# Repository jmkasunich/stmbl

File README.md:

Build Log: https://travis-ci.org/rene-dev/stmbl

DISCLAIMER
===

THE AUTHORS OF THIS SOFTWARE ACCEPT ABSOLUTELY NO LIABILITY FOR
ANY HARM OR LOSS RESULTING FROM ITS USE.  IT IS _EXTREMELY_ UNWISE
TO RELY ON SOFTWARE ALONE FOR SAFETY.  Any machinery capable of
harming persons must have provisions for completely removing power
from all motors, etc, before persons enter any danger area.  All
machinery must be designed to comply with local and national safety
codes, and the authors of this software can not, and do not, take
any responsibility for such compliance.

This software is released under the GPLv3.

stmbl
=====

IMPORTANT:  This fork should **NOT** be used to make PC boards.
The board layout files have been reverted to work with the stable version of Kicad, which affects the copper.  At some point I will probably clean up the resulting issues, but that is not a priority.  I simply want to be able to view the layout using the stable version.

There is a wiki. https://github.com/rene-dev/stmbl/wiki
There will be documentation.

**IRC: #stmbl on irc.hackint.eu**
https://webirc.hackint.org/#stmbl

stmbl is an open source servo drive designed for Retrofitting CNC machines and Robots. It supports Industrial AC and DC servos with up to 320V and 2kW (see [specs](https://github.com/rene-dev/stmbl/wiki/specs) for details).

Documentation about the PCB and pinout of the feedback connector:

https://github.com/rene-dev/stmbl/wiki/Pinouts

https://github.com/rene-dev/stmbl/wiki/PCB

##### Hardware version 4.0

##### Driving a Bosch Turboscara
https://www.youtube.com/watch?v=d6NH1W7DUnQ

##### Driving a Manutec Robot
https://www.youtube.com/watch?v=gwgnAeGjZrA  
https://www.youtube.com/watch?v=wXLcAZwjlzE

##### Drivetest
https://www.youtube.com/watch?v=-E1o_5cFyto

#### Supported Motors
* Synchronous AC Servos
* DC Servos
* 2 Phase HF spindle motors
* IRAMX Hardware testet up to 320V

#### Supported Feedback systems
* Resolvers
* Incremental encoders
* sin/cos encoder interpolation
* Mitsubishi absolute encoders
* Sanyo Denki absolute encoders
* Yaskawa absolute encoders
* Sick HIPERFACE®

##### Planned:
* EnDat
* BiSS
* SSI
* Sanyo Denki wire-saving incremental encoder

#### Supported Position/Velocity Commands Inputs:
* Smartserial
* Quadrature
* Step/direction
* RS485

#### TODO
* AC Async

#### Directories
* hw/eagle/ Eagle board files and schematics
* hw/spice/ Spice simulation for resolver interface
* src/ STM32F4 code, command, feedback and control loop
* stm32f103/ STM32F1 code, running on the HV side, generating PWM
* bootloader/ bootloader for the f4

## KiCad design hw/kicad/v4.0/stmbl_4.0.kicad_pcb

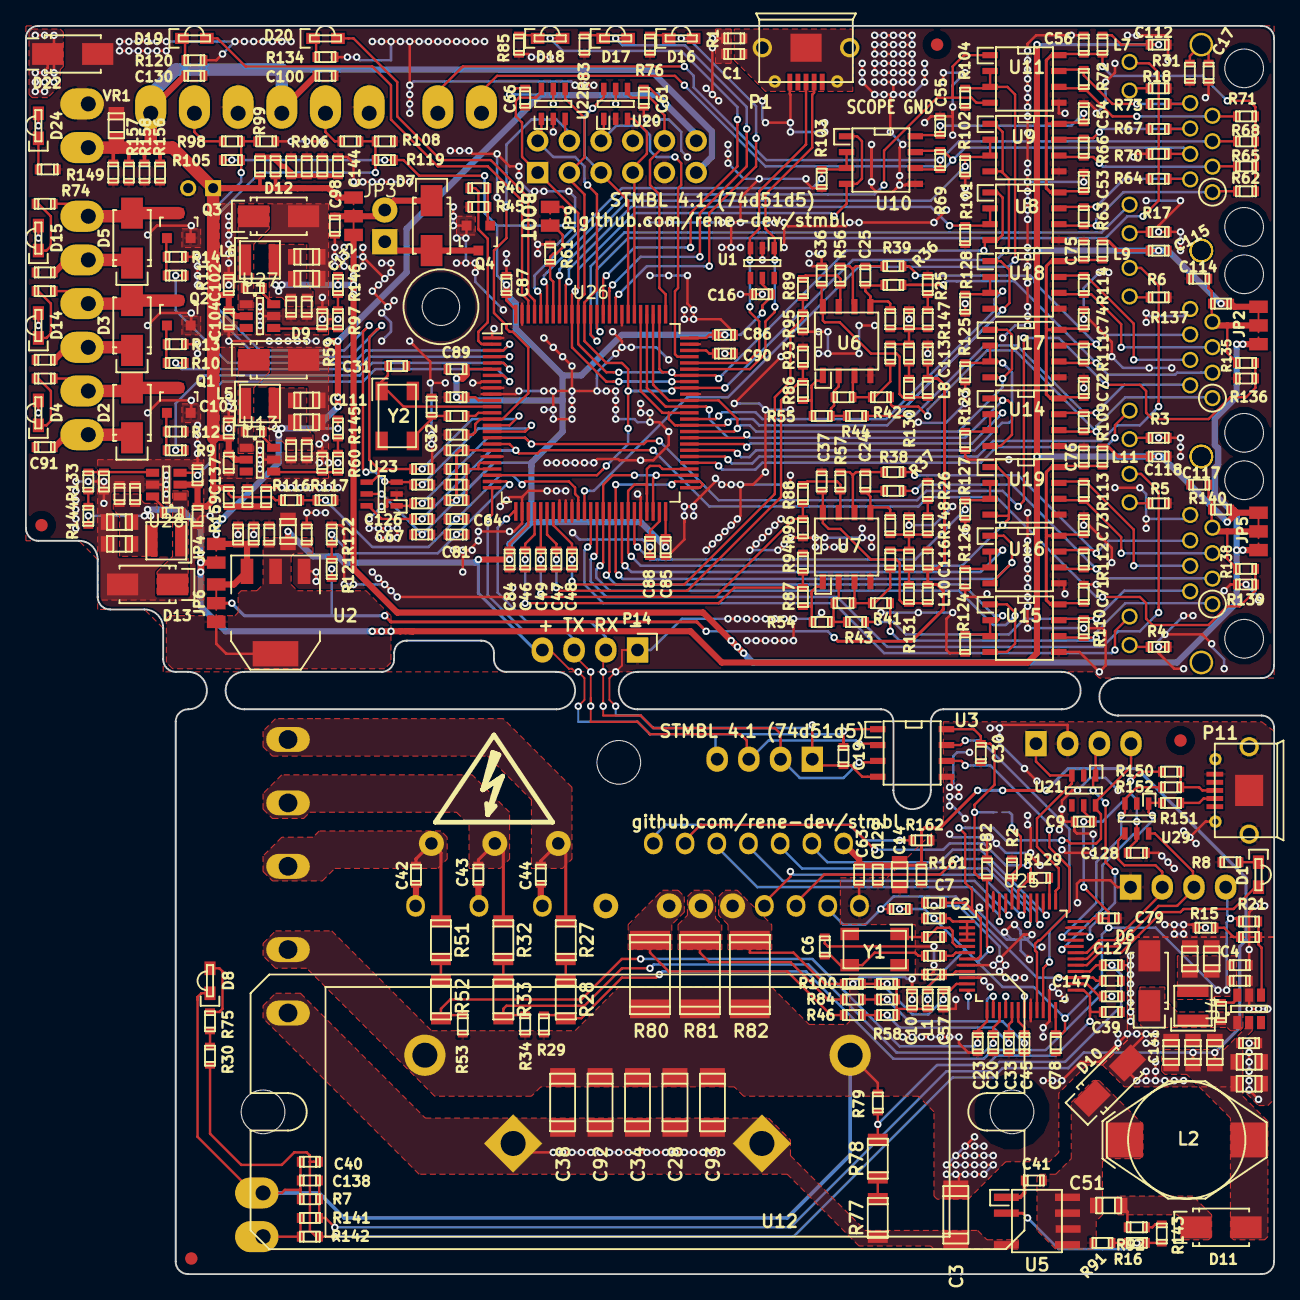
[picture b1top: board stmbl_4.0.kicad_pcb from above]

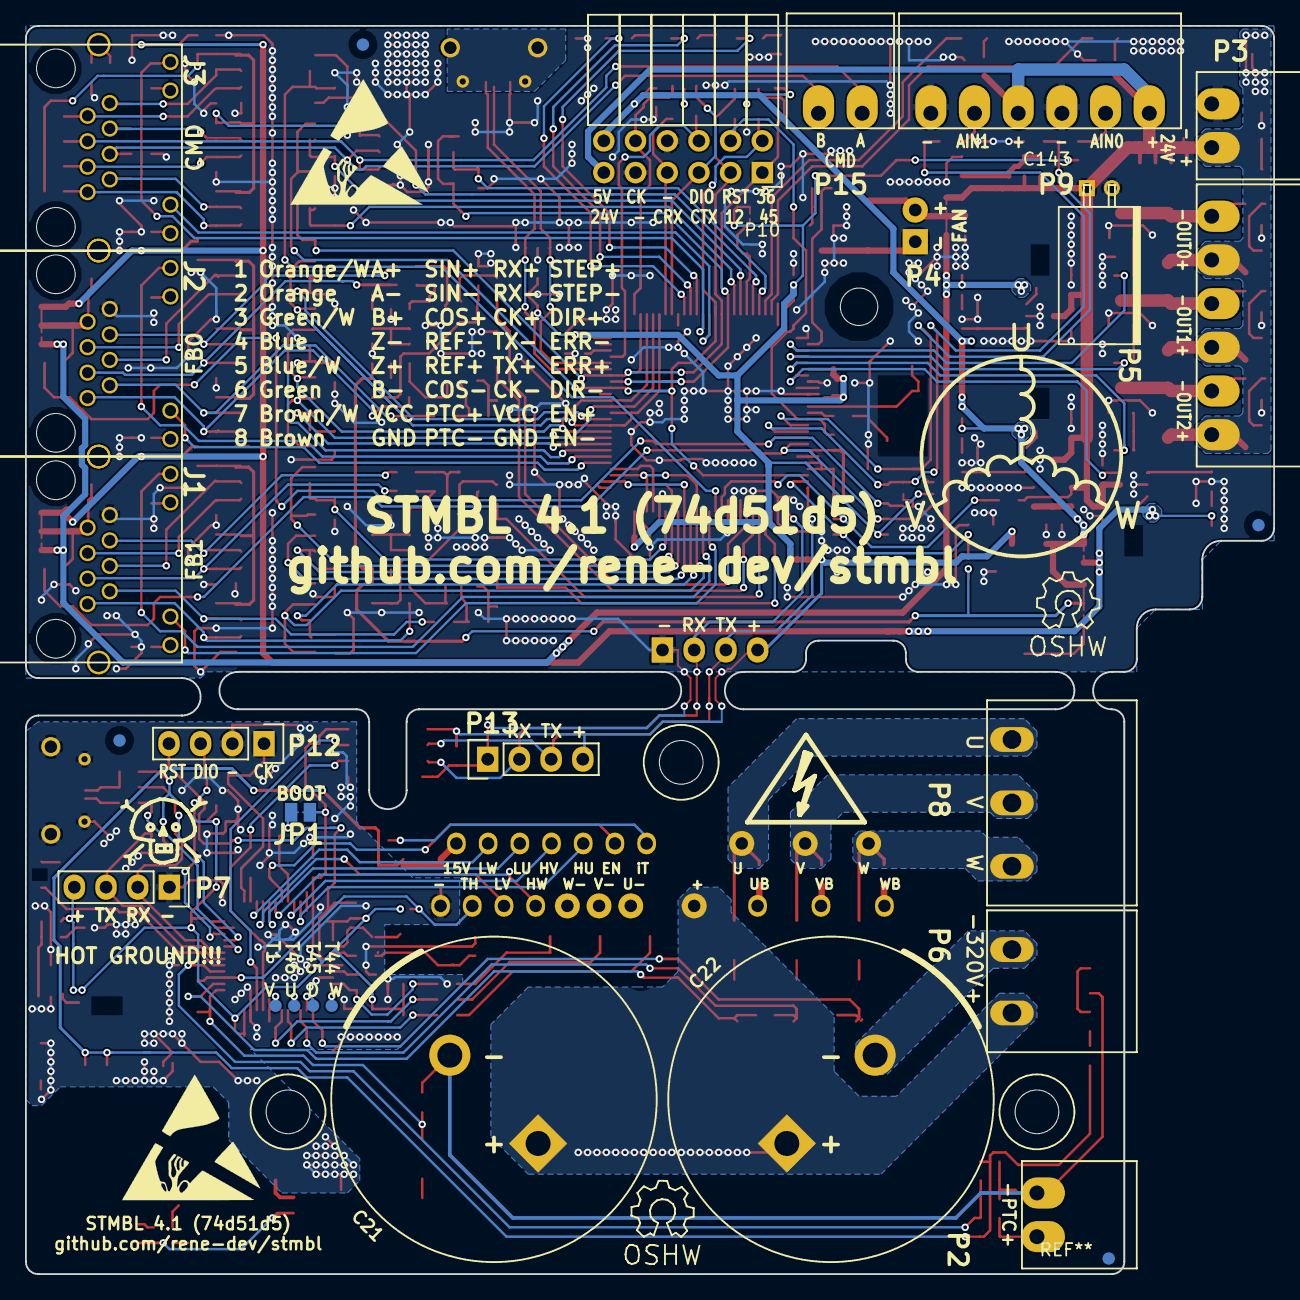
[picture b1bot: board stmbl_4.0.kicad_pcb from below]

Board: 2 copper layers, 100.0 x 100.0 mm, 411 parts (28 on the bottom side), 226 nets.

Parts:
C1, C2, C7, C9, C10, C12, C13, C15, C16, C17, C19, C29, C30, C36, C37, C40, C41, C53, C54, C55, C56, C58, C60, C61, C63, C66, C67, C71, C72, C73, C74, C75, C76, C77, C78, C79, C80, C82, C83, C84, C85, C86, C87, C89, C91, C94, C95, C96, C98, C99, C100, C103, C104, C105, C106, C107, C108, C112, C113, C114, C115, C116, C117, C118, C119, C120, C121, C122, C125, C126, C127, C128, C130, C138, C147: 100n; C_0603
C3, C28, C34, C38, C92, C93: 150n; C_1808
C4, C14, C35, C51, C68, C69, C70, C97, C109, C110, C111, C123, C124, C131, C132, C141: 10µ; C_0805
C5, C6, C11, C20, C23, C24, C25, C26, C27, C31, C32, C33, C39, C45, C57: 18p; C_0603
C8, C18, C42, C43, C44, C50, C62, C65, C88, C90, C101, C102, C129, C133, C134, C135, C136, C137, C139, C140, C142, C144: 2.2µ; C_0603
C21, C22: 270µ; C_Radial_D26_L45_P10
C46, C47, C48, C49, C52, C59, C64, C81: 1n; C_0603
C143: 22µ; C_Radial_D6.5_L11_P2.5
D1, D16: red; LED-0805-SIDE
D2, D3, D5, D7, D10, D11: ES1J R2; SMA_Standard
D4, D8, D14, D15, D18, D19, D20, D24: green; LED-0805-SIDE
D6, D9, D12, D13: SS34A; SMA_Standard
D17: yellow; LED-0805-SIDE
D22: SMAJ24A TVS 24V; SMA_Standard
J1, J2, J3: RJ45_LED
JP1, JP4, JP9: Jumper_NO_Small; SOLDER_JUMPER
JP2, JP3, JP5, JP6: JUMPER3_NC; SOLDER_JUMPER_3_NC
L1, L3, L7, L8, L9, L10, L11: 220r 700mA; R_0603
L2: 1m 250mA; NPI31W
L4, L5, L6, L12: 4.7µH 1.5A; SMD_INDUCTOR_32x25
LOGO1, LOGO1#2: OPEN_HARDWARE_1; Symbol_OSHW-Logo_SilkScreen
P1, P11: USB_OTG; USB_Micro-B
P2, P3, P15: CONN_01X02; akl182-2
P4: CONN_01X02; Pin_Header_Angled_1x02
P5, P9: CONN_01X06; akl182-6
P6: CONN_01X02; RM5.08_1x2
P7, P12: CONN_01X04; Pin_Header_Straight_1x04
P8: CONN_01X03; RM5.08_1x3
P10: CONN_02X06; Socket_Strip_Angled_2x06
P13: CONN_01X04; Socket_Strip_Straight_1x04
P14: CONN_01X04; Pin_Header_Angled_1x04
Q1, Q2, Q3, Q4: IRLML6344; SOT-23
R1, R23, R24, R25, R26, R31, R109, R110, R111, R112, R113, R114, R130, R131: 120; R_0603
R2, R12, R13, R14, R15, R16, R30, R45, R61, R63, R66, R69, R72, R75, R91, R99, R101, R102, R103, R104, R105, R108, R117, R118, R119, R121, R122, R123, R124, R125, R126, R127, R128, R129, R136, R139, R144, R145, R146, R153, R162: 1k; R_0603
R3, R4, R5, R6, R8, R17, R18, R46, R76, R83, R84, R85, R93, R94, R95, R96, R100, R120, R134: 470; R_0603
R7, R35, R36, R37, R38, R39, R41, R42, R43, R44, R62, R64, R65, R67, R68, R70, R71, R73, R98, R106, R115, R116, R132, R135, R137, R138, R140, R142, R155, R156, R157, R158: 10k; R_0603
R9, R10, R11, R40, R86, R87, R88, R89, R147, R148, R151, R152, R154, R159, R160: 22; R_0603
R19, R47, R48, R49, R50, R54, R55, R56, R57, R58, R90, R92, R107: 15k; R_0603
R20, R22, R29, R34, R53, R59, R74, R79, R149, R161: 3.9k; R_0603
R21, R60, R97, R133, R141: 51k; R_0603
R27, R28, R32, R33, R51, R52, R77, R78: 249k; R_1206
R80, R81, R82: 0.003; R_2512
R143, R150: 1.5k; R_0603
T1, T44, T45, T46: testpoint; Measurement_Point_Round-SMD-Pad_Small
U1, U20, U21, U22, U23, U29: USBLC6-4SC6; SOT-23-6
U2: zldo1117; SOT-223
U3: SI8621; SOIC-8-N
U4, U13, U27, U28: ACT4088; SOT-23-6
U5: lnk304D; SOIC-7
U6, U7: LM358; SOIC-8-N
U8, U9, U10, U11, U14, U15, U16, U17, U18, U19: SN65176B; SOIC-8-N
U12: IRAM256a; IRAM256
U24, U30, U31, U32: non_plated; non_plated_3mm
U25: STM32F303CBTx; LQFP-48_7x7mm_Pitch0.5mm
U26: STM32F405VG; LQFP-100_14x14mm_Pitch0.5mm
VR1: 24V; R_0805
Y1, Y2: 8M; Crystal_SMD_0503_4Pads

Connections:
+3.3VP: C2.1, C4.1, C9.1, C10.2, C30.2, C35.1, C50.1, C60.1, C78.2, C79.2, C82.2, C128.1, JP1.1, L1.2, L4.2, P7.4, R21.1, R58.2, R90.2, R107.2, R115.1, R150.2, U3.8, U21.5, U25.1, U25.2, U25.3, U25.4, U25.24, U25.36, U25.48, U29.5
+3V3: C16.2, C18.1, C19.1, C67.1, C77.2, C80.2, C84.2, C85.2, C86.2, C87.2, C89.2, C99.1, C131.1, JP6.3, JP9.1, L3.2, P13.4, P14.4, R105.1, R119.1, U1.5, U2.2, U3.1, U23.5, U26.6, U26.11, U26.19, U26.28, U26.50, U26.75, U26.100
+5F: C112.1, C115.2, C118.2, C122.1, C123.1, C124.1, C134.1, JP2.1, JP4.1, JP5.1, L7.2, L9.1, L11.1, L12.2, R137.2, R140.2, R144.1
+5V: C8.1, C61.1, C66.1, C96.1, C107.1, C109.1, C111.1, C135.1, JP4.2, JP6.1, L5.2, P10.12, R145.1, U2.3, U20.5, U22.5
+5VA: C113.2, C116.2, JP6.2, L8.1, L10.1, R121.1
+12V: C108.1, C110.1, C132.1, C136.1, JP2.3, JP3.1, JP5.3, L6.2, R146.1
+15V: C14.2, C40.2, C58.1, C63.1, C68.1, C69.1, C70.1, C97.1, C129.1, C141.1, D11.2, L2.2, R30.1, R142.1, R161.1, U4.2, U12.28
+24V: C91.1, C94.1, C95.1, C100.1, C102.1, C103.1, C104.1, C120.1, C130.1, C133.1, C137.1, C143.1, D2.1, D3.1, D4.2, D5.1, D14.2, D15.2, D22.1, D24.2, JP3.3, P3.1, P5.1, P5.3, P5.5, P9.1, P9.4, P10.11, R116.1, R154.1, R155.1, R156.1, R157.1, R158.1, R159.1, R160.1, U13.2, U27.2, U28.2, VR1.1
/ctrl/FB0/A12: C47.1, R86.1, R93.1, U26.31
/ctrl/FB0/A35: C48.1, R89.1, R95.1, U26.32
/ctrl/FB0/A78: C125.1, R135.2, R136.1, U23.1, U26.17
/ctrl/FB0/D12: U14.1, U14.4, U26.59, U26.64, U26.79
/ctrl/FB0/D36: U17.1, U17.4, U26.60, U26.65, U26.78
/ctrl/FB0/D45: U18.1, U18.4, U26.61, U26.63, U26.80
/ctrl/FB0/E12: R123.1, U14.2, U14.3, U26.58
/ctrl/FB0/E36: R125.1, U17.2, U17.3, U26.57
/ctrl/FB0/E45: R128.1, U18.2, U18.3, U26.62
/ctrl/FB1/A12: C46.1, R87.1, R94.1, U26.29
/ctrl/FB1/A35: C49.1, R88.1, R96.1, U26.30
/ctrl/FB1/A78: C126.1, R138.2, R139.1, U23.6, U26.18
/ctrl/FB1/D12: U15.1, U15.4, U26.40, U26.48, U26.53
/ctrl/FB1/D36: U16.1, U16.4, U26.42, U26.51, U26.52
/ctrl/FB1/D45: U19.1, U19.4, U26.44, U26.47, U26.54
/ctrl/FB1/E12: R124.1, U15.2, U15.3, U26.41
/ctrl/FB1/E36: R126.1, U16.2, U16.3, U26.43
/ctrl/FB1/E45: R127.1, U19.2, U19.3, U26.45
/ctrl/IO/CAN_RX: P10.7, U20.3, U26.81
/ctrl/IO/CAN_TX: P10.5, U20.6, U26.82
/ctrl/IO/IO_FAN: R40.2, U26.2
/ctrl/IO/IO_GREEN: D18.2, U26.86
/ctrl/IO/IO_L0: D19.2, U26.98
/ctrl/IO/IO_L1: D20.2, U26.97
/ctrl/IO/IO_OUT0: R11.2, U26.3
/ctrl/IO/IO_OUT1: R10.2, U26.4
/ctrl/IO/IO_OUT2: R9.2, U26.5
/ctrl/IO/IO_RED: D16.2, U26.84
/ctrl/IO/IO_YELLOW: D17.2, U26.85
/ctrl/IO/NRST: C29.2, P10.4, U22.3, U26.14
/ctrl/IO/SWCK: P10.10, U20.4, U26.76
/ctrl/IO/SWDIO: P10.6, U20.1, U26.72
/ctrl/RX: P13.2, P14.2, U3.3, U26.26
/ctrl/TX: P13.3, P14.3, U3.2, U26.25
/ctrl/f4/A_5V: C81.1, R121.2, R122.1, U26.24
/ctrl/f4/A_24V: C64.1, R116.2, R117.1, U26.36
/ctrl/f4/CMD_12: P10.3, U8.1, U8.4, U22.4, U26.69, U26.77, U26.90
/ctrl/f4/CMD_12E: R101.1, U8.2, U8.3, U26.92
/ctrl/f4/CMD_36: P10.2, U9.1, U9.4, U22.1, U26.23, U26.67, U26.89
/ctrl/f4/CMD_36E: R102.1, U9.2, U9.3, U26.93
/ctrl/f4/CMD_45: P10.1, U10.1, U10.4, U22.6, U26.68, U26.91
/ctrl/f4/CMD_45E: R103.1, U10.2, U10.3, U26.96
/ctrl/f4/CMD_78: U11.1, U11.4, U26.95
/ctrl/f4/CMD_78E: R104.1, U11.2, U11.3, U26.37
/ctrl/f4/CMD_L1: J3.12, U26.88
/ctrl/f4/CMD_L2: J3.10, U26.87
/ctrl/f4/EN_5V: U26.7, U28.3
/ctrl/f4/FB0_L1: J2.12, U26.55
/ctrl/f4/FB0_L2: J2.10, U26.56
/ctrl/f4/FB1_L1: J1.12, U26.38
/ctrl/f4/FB1_L2: J1.10, U26.39
/ctrl/f4/IO_AIN0: C52.1, R98.2, R99.1, R105.2, U23.4, U26.15
/ctrl/f4/IO_AIN1: C59.1, R106.2, R108.1, R119.2, U23.3, U26.16
/hv/back-emf/U: C44.1, P8.1, R27.1, U12.10
/hv/back-emf/V: C43.1, P8.2, R32.1, U12.6
/hv/back-emf/W: C42.1, P8.3, R51.1, U12.2
/hv/cur/A_IU: C33.1, R46.1, R58.1, U25.17
/hv/cur/A_IV: C45.1, R84.1, R90.1, U25.18
/hv/cur/A_IW: C57.1, R100.1, R107.1, U25.11
/hv/driver/CUH: R46.2, R80.1, U12.17
/hv/driver/CVH: R81.1, R84.2, U12.19
/hv/driver/CWH: R82.1, R100.2, U12.21
/hv/driver/HU: U12.20, U25.46
/hv/driver/HV: U12.22, U25.45
/hv/driver/HW: U12.23, U25.42
/hv/driver/LU: U12.24, U25.41
/hv/driver/LV: U12.25, U25.40
/hv/driver/LW: U12.26, U25.39
/hv/driver/itirp: R162.1, U12.16
/hv/f3/A_HV: C39.1, R78.2, R79.1, U25.25
/hv/f3/A_T_HV: C147.1, R115.2, U12.27, U25.27
/hv/f3/A_T_MOT: C127.2, C138.2, R7.2, R141.2, U25.28
/hv/f3/A_U: C11.1, R28.2, R29.1, U25.26
/hv/f3/A_V: C20.1, R33.2, R34.1, U25.15
/hv/f3/A_W: C23.1, R52.2, R53.1, U25.13
/hv/f3/HV_EN: R129.1, U12.18, U25.43
/hv/f3/HV_RX: U3.7, U25.22
/hv/f3/HV_TX: U3.6, U25.21
/hv/f3/IO_RX: P7.2, U25.31, U29.4
/hv/f3/IO_TX: P7.3, U25.30, U29.6
/hv/f3/NRST: C7.1, P12.4, U21.6, U25.7
/hv/f3/SWCLK: P12.1, U21.3, U25.37
/hv/f3/SWDIO: P12.3, U21.1, U25.34
/hv/f3/USB_DM: R151.1, U25.32, U29.1
/hv/f3/USB_DP: R152.1, U25.33, U29.3
GND: C1.2, C8.2, C12.2, C13.2, C16.1, C17.2, C18.2, C19.2, C29.1, C31.2, C32.2, C36.1, C37.1, C46.2, C47.2, C48.2, C49.2, C52.2, C53.2, C54.2, C55.2, C56.2, C59.2, C61.2, C62.2, C64.2, C65.1, C66.2, C67.2, C71.2, C72.2, C73.2, C74.2, C75.2, C76.2, C77.1, C80.1, C81.2, C84.1, C85.1, C86.1, C87.1, C88.2, C89.1, C90.2, C91.2, C94.2, C95.2, C96.2, C98.2, C99.2, C100.2, C101.2, C102.2, C103.2, C104.2, C107.2, C108.2, C109.2, C110.2, C111.2, C112.2, C113.1, C114.2, C115.1, C116.1, C117.2, C118.1, C119.1, C120.2, C122.2, C123.2, C124.2, C125.2, C126.2, C130.2, C131.2, C132.2, C133.2, C134.2, C135.2, C136.2, C137.2, C139.2, C140.2, C142.2, C143.2, C144.2, D9.2, D12.2, D13.2, D22.2, J1.8, J2.8, P1.5, P3.2, P9.3, P9.6, P10.8, P10.9, P13.1, P14.1, Q1.2, Q2.2, Q3.2, Q4.2, R1.2, R3.2, R4.2, R5.2, R6.2, R12.2, R13.2, R14.2, R17.2, R18.2, R25.2, R26.2, R31.2, R35.2, R45.2, R59.2, R61.1, R64.2, R67.2, R70.2, R73.2, R76.2, R83.2, R85.2, R93.2, R94.2, R95.2, R96.2, R99.2, R101.2, R102.2, R103.2, R104.2, R108.2, R117.2, R120.2, R122.2, R123.2, R124.2, R125.2, R126.2, R127.2, R128.2, R132.2, R134.2, R136.2, R139.2, R149.2, R155.2, R156.2, R157.2, R158.2, U1.2, U2.1, U3.4, U6.4, U7.4, U8.5, U9.5, U10.5, U11.5, U13.5, U14.5, U15.5, U16.5, U17.5, U18.5, U19.5, U20.2, U22.2, U23.2, U26.1, U26.8, U26.9, U26.10, U26.20, U26.27, U26.33, U26.34, U26.35, U26.46, U26.66, U26.74, U26.83, U26.99, U27.5, U28.5, VR1.2
GNDD: C17.1, J1.13, J2.13, J3.13, R31.1
GNDPWR: C2.2, C3.2, C4.2, C5.2, C6.2, C7.2, C9.2, C10.1, C11.2, C14.1, C20.2, C21.2, C22.2, C23.2, C28.2, C30.1, C33.2, C34.2, C35.2, C38.2, C39.2, C40.1, C45.2, C50.2, C57.2, C58.2, C60.2, C63.2, C68.2, C69.2, C70.2, C78.1, C79.1, C82.1, C83.1, C92.2, C93.2, C97.2, C127.1, C128.2, C129.2, C138.1, C141.2, C147.2, D6.2, D8.1, D10.2, P2.2, P6.1, P7.1, P11.5, P11.6, P12.2, R2.2, R7.1, R8.1, R15.2, R29.2, R34.2, R53.2, R79.2, R80.2, R81.2, R82.2, R161.2, R162.2, U3.5, U4.5, U12.29, U21.2, U25.8, U25.10, U25.20, U25.23, U25.35, U25.47, U29.2
unnamed: C1.1, P1.6, R1.1
unnamed: C5.1, U25.5, Y1.1
unnamed: C6.1, R118.2, Y1.2
unnamed: C12.1, R23.2, R48.1, R49.1, R148.1
unnamed: C13.1, R24.2, R47.1, R50.1, R147.1
unnamed: C15.1, U4.6
unnamed: C15.2, D6.1, L4.1, U4.1
unnamed: C24.1, R37.1, R49.2, U7.5
unnamed: C24.2, R38.1, R57.2, U7.6
unnamed: C25.1, R36.1, R50.2, U6.5
unnamed: C25.2, R39.1, R56.2, U6.6
unnamed: C26.1, R41.1, R48.2, U7.3
unnamed: C26.2, R43.1, R54.2, U7.2
unnamed: C27.1, R42.1, R47.2, U6.3
unnamed: C27.2, R44.1, R55.2, U6.2
unnamed: C31.1, U26.12, Y2.1
unnamed: C32.1, R153.2, Y2.2
unnamed: C36.2, L8.2, R130.1, U6.8
unnamed: C37.2, L10.2, R131.1, U7.8
unnamed: C41.1, U5.1
unnamed: C41.2, C51.2, D10.1, L2.1, R91.1, U5.5, U5.6, U5.7, U5.8
unnamed: C42.2, U12.1
unnamed: C43.2, U12.5
unnamed: C44.2, U12.9
unnamed: C51.1, D11.1, R92.2
unnamed: C53.1, C54.1, C55.1, C56.1, L7.1, R62.1, R65.1, R68.1, R71.1, U8.8, U9.8, U10.8, U11.8
unnamed: C71.1, C73.1, C76.1, L11.2, U15.8, U16.8, U19.8
unnamed: C72.1, C74.1, C75.1, L9.2, U14.8, U17.8, U18.8
unnamed: C83.2, L1.1, U25.9
unnamed: C88.1, U26.49
unnamed: C90.1, U26.73
unnamed: C98.1, D7.1, JP3.2, P4.2
unnamed: C62.1, C101.1, R159.2
unnamed: C105.1, U13.6
unnamed: C105.2, D9.1, L5.1, U13.1
unnamed: C106.1, U27.6
unnamed: C106.2, D12.1, L6.1, U27.1
unnamed: C114.1, J2.7, JP2.2, R135.1, R137.1
unnamed: C117.1, J1.7, JP5.2, R138.1, R140.1
unnamed: C65.2, C119.2, L3.1, U26.21, U26.22
unnamed: C121.1, U28.6
unnamed: C121.2, D13.1, L12.1, U28.1
unnamed: C139.1, C140.1, C142.1, C144.1, R154.2, R160.2
unnamed: D1.1, R8.2
unnamed: D1.2, U25.29
unnamed: D2.2, P5.2, Q1.3, R20.2
unnamed: D3.2, P5.4, Q2.3, R22.2
unnamed: D4.1, R20.1
unnamed: D5.2, P5.6, Q3.3, R74.2
unnamed: D7.2, P4.1, Q4.3
unnamed: D8.2, R75.2
unnamed: D14.1, R22.1
unnamed: D15.1, R74.1
unnamed: D16.1, R76.1
unnamed: D17.1, R83.1
unnamed: D18.1, R85.1
unnamed: D19.1, R120.1
unnamed: D20.1, R134.1
unnamed: D24.1, R149.1
unnamed: J1.1, R41.2, R110.1, U15.6
unnamed: J1.2, R43.2, R110.2, U15.7
unnamed: J1.3, R37.2, R112.1, U16.6
unnamed: J1.4, R113.2, U19.7
unnamed: J1.5, R113.1, U19.6
unnamed: J1.6, R38.2, R112.2, U16.7
unnamed: J1.9, R5.1
unnamed: J1.11, R4.1
unnamed: J2.1, R42.2, R109.1, U14.6
unnamed: J2.2, R44.2, R109.2, U14.7
unnamed: J2.3, R36.2, R111.1, U17.6
unnamed: J2.4, R114.2, U18.7
unnamed: J2.5, R114.1, U18.6
unnamed: J2.6, R39.2, R111.2, U17.7
unnamed: J2.9, R6.1
unnamed: J2.11, R3.1
unnamed: J3.1, R62.2, R63.1, U8.6
unnamed: J3.2, R63.2, R64.1, U8.7
unnamed: J3.3, R65.2, R66.1, U9.6
unnamed: J3.4, P15.2, R69.2, R70.1, U10.7
unnamed: J3.5, P15.1, R68.2, R69.1, U10.6
unnamed: J3.6, R66.2, R67.1, U9.7
unnamed: J3.7, R71.2, R72.1, U11.6
unnamed: J3.8, R72.2, R73.1, U11.7
unnamed: J3.9, R18.1
unnamed: J3.11, R17.1
unnamed: JP1.2, R2.1, U25.44
unnamed: JP9.2, R61.2, U26.94
unnamed: P1.2, U1.1, U26.70
unnamed: P1.3, U1.3, U26.71
unnamed: P2.1, R141.1, R142.2
unnamed: P9.2, R98.1
unnamed: P9.5, R106.1
unnamed: P11.2, R151.2
unnamed: P11.3, R150.1, R152.2
unnamed: Q1.1, R9.1, R12.1
unnamed: Q2.1, R10.1, R13.1
unnamed: Q3.1, R11.1, R14.1
unnamed: Q4.1, R40.1, R45.1
unnamed: R15.1, R19.2
unnamed: R16.1, R91.2
unnamed: R19.1, R21.2, U4.4
unnamed: R27.2, R28.1
unnamed: R30.2, R75.1
unnamed: R32.2, R33.1
unnamed: R35.1, R60.2, U13.4
unnamed: R51.2, R52.1
unnamed: R54.1, R87.2, U7.1
unnamed: R55.1, R86.2, U6.1
unnamed: R56.1, R89.2, U6.7
unnamed: R57.1, R88.2, U7.7
unnamed: R59.1, R97.2, U27.4
unnamed: R77.2, R78.1
unnamed: R118.1, U25.6
unnamed: R129.2, U25.38
unnamed: R24.1, R130.2
unnamed: R23.1, R131.2
unnamed: R132.1, R133.2, U28.4
unnamed: R133.1, R144.2
unnamed: R16.2, R143.1, U5.2
unnamed: R92.1, R143.2
unnamed: R60.1, R145.2
unnamed: R97.1, R146.2
unnamed: R25.1, R147.2
unnamed: R26.1, R148.2
unnamed: R153.1, U26.13
unnamed: T1.1, U25.19
unnamed: T44.1, U25.12
unnamed: T45.1, U25.14
unnamed: T46.1, U25.16
VPP: C3.1, C21.1, C22.1, C28.1, C34.1, C38.1, C92.1, C93.1, P6.2, R77.1, U5.4, U12.13

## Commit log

2017-11-20 make pcb file compatible with Kicad stable version
    Removed diff_pair and roundrect attributes from file.
    Changed roundrect to rect. Diff pair was present but not used.
2017-11-21 add warning note - PCB files should not be used to make actual boards
    I reverted the PCB files to work with Kicad Stable. I do not
    intend to make boards from this fork, instead I am working on
    a related project (multistmbl) and simply need to be able to
    view the stmbl layouts.
